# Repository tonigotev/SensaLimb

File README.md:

# SensaLimb

Smart arm prosthesis project.

## ML Model (Latest Recommended): Toro Ossaba Conv1D

Use this model family as the current default:

- Model family folder: `ML/models/conv1d_angle_toro_ossaba`
- Dataset folder (required): `ML/datasets/Toro Ossaba`
- Training script: `ML/train/train_conv1d_angle_toro_ossaba.py`

## 1) Install ML dependencies

From the repository root (PowerShell):

```powershell
python -m pip install --upgrade pip
python -m pip install -r requirements-ml.txt
```

## 2) Download and extract the Toro Ossaba dataset (required)

Dataset source:

- https://zenodo.org/records/7946782

Extract location must be exactly:

- `ML/datasets/Toro Ossaba`

Important extraction rule:

- After extraction, your `.txt` dataset files must be inside `ML/datasets/Toro Ossaba/...` (subject subfolders).
- Do **not** leave the files nested one level too deep (for example, avoid `ML/datasets/Toro Ossaba/Toro Ossaba/...`).

Quick check (PowerShell):

```powershell
Get-ChildItem "ML/datasets/Toro Ossaba" -Recurse -Filter *.txt | Select-Object -First 5 FullName
```

## 3) Install/extract the Toro Ossaba trained model files

If you received model files as a zip/archive, extract them into:

- `ML/models/conv1d_angle_toro_ossaba`

Expected model artifacts in the selected run folder:

- `model.keras`
- `model.tflite`
- `model_int8.tflite` (optional but recommended for embedded use)
- `meta.json`

Example expected path pattern:

- `ML/models/conv1d_angle_toro_ossaba/<run_name>/model.tflite`

If your extraction creates an extra folder level, move files so that the run folder directly contains `meta.json` and model files.

## 4) Run the model (inference/validation)

Pick your run folder (example):

```powershell
$MODEL_DIR = "ML/models/conv1d_angle_toro_ossaba/seed9_20260117_034451_884"
```

### A. Compare float vs int8 model outputs

```powershell
python ML/tools/compare_tflite_models.py --model-dir "$MODEL_DIR" --input-root "ML/datasets/Toro Ossaba" --samples 50
```

### B. Generate prediction-vs-true plots

```powershell
python ML/tools/plot_tflite_pred_vs_true.py --model-dir "$MODEL_DIR" --input-root "ML/datasets/Toro Ossaba" --samples 2000
```

Output images are saved in the same run folder:

- `pred_vs_true_float.png`
- `pred_vs_true_int8.png`

## 5) (Optional) Train a new Toro Ossaba model run

```powershell
python ML/train/train_conv1d_angle_toro_ossaba.py --use-file-split --movement all --emg-source filtered --angle-history-sec 0.1 --tflite-int8 --seed 9 --run-name seed9_new
```

This creates a new run folder under `ML/models/conv1d_angle_toro_ossaba`.

## Common setup mistakes

- Dataset extracted to wrong folder (must be `ML/datasets/Toro Ossaba`).
- Extra nested folder after extraction.
- Model archive extracted to wrong location.
- Missing `model.tflite` / `meta.json` in selected run folder.

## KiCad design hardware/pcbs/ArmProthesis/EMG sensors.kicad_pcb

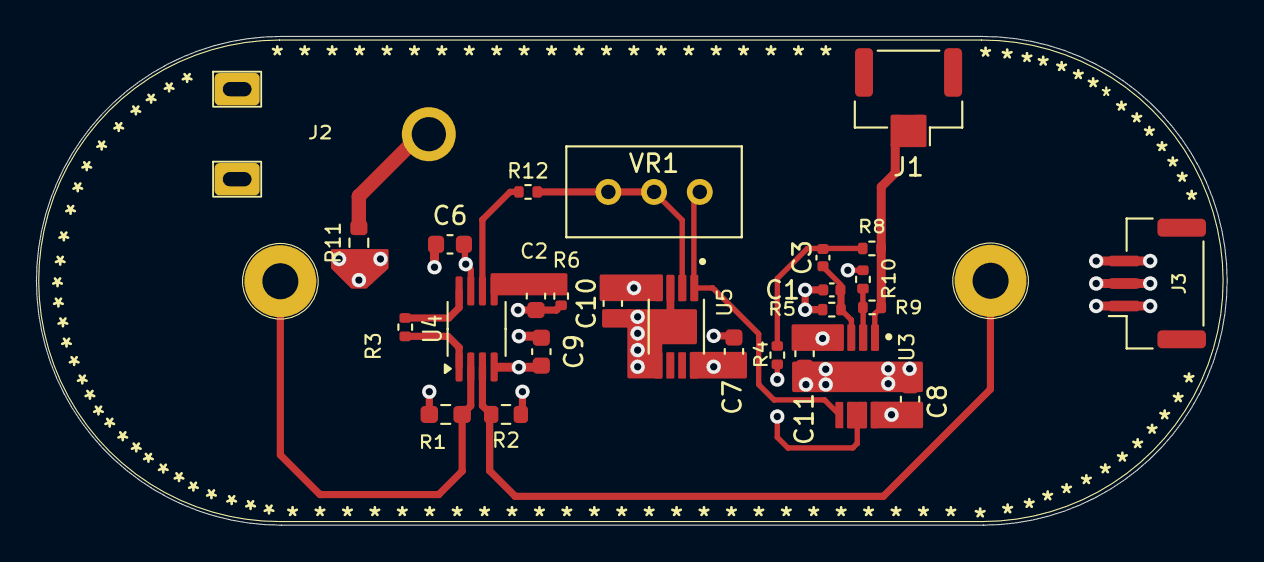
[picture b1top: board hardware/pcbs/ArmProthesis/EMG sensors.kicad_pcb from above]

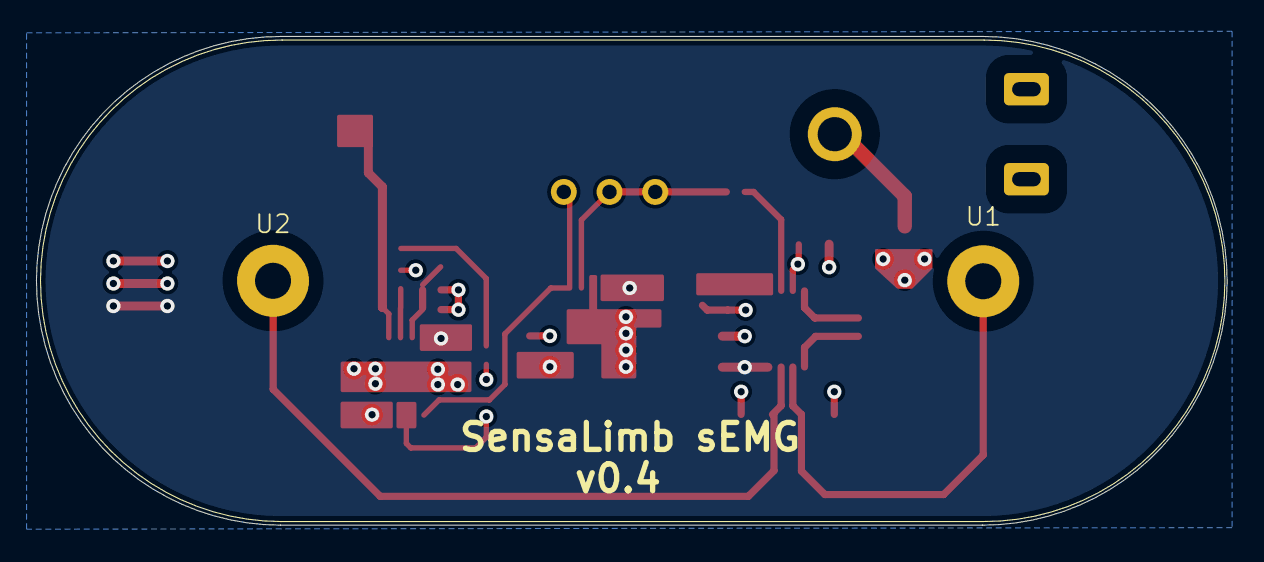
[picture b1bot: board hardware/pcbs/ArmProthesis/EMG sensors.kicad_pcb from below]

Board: 4 copper layers, 66.2 x 27.1 mm, 29 parts (2 on the bottom side), 17 nets.

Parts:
C1: 10uF; C_0402_1005Metric
C2: DNP; C_0603_1608Metric
C3: 330nF; C_0402_1005Metric
C6, C7, C8, C9, C10, C11: 1uF; C_0603_1608Metric
J1: Conn_01x02_Pin; JST_GH_SM02B-GHS-TB_1x02-1MP_P1.25mm_Horizontal
J2: DNP; DIN_Male_1PIN_1.5mm
J3: Conn_01x03_Pin; JST_GH_SM03B-GHS-TB_1x03-1MP_P1.25mm_Horizontal
R1: 10M; R_0603_1608Metric_Pad0.98x0.95mm_HandSolder
R2: 10M; R_0603_1608Metric
R3: 2k; R_0402_1005Metric
R4, R5, R8, R10: 1k; R_0402_1005Metric
R6: 249k; R_0402_1005Metric
R9, R12: 10k; R_0402_1005Metric
R11: 1M; R_0603_1608Metric
U1, U2: EMG_Snap_4mm
U3, U5: LME49726MY
U4: INA326; MSOP-8_3x3mm_P0.65mm
VR1: 100k; Potentiometer_Bourns_3296W_Vertical

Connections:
/+2.5V: C6.1, C7.1, C8.1, J3.3, R11.1, U3.8 (VDD), U4.7 (V+), U5.8 (VDD)
/-2.5V: C9.1, C10.1, C11.1, J3.1, U3.4 (VSS), U4.4 (V-), U5.4 (VSS)
/AEMG: J1.1, J1.2, R8.1, R9.2, U3.1 (OUT_A)
FB: R9.1, R10.2, U3.2 (NEGA)
GND: C1.1, C2.1, C6.2, C7.2, C8.2, C9.2, C10.2, C11.2, J3.2, R1.1, R2.1, R5.1, R6.1, R10.1, U3.9 (EP), U5.3 (POSA), U5.5 (POSB), U5.9 (EP)
INVERTED: U3.5 (POSB), U5.1 (OUT_A), VR1.3
unnamed: C3.2, R4.2, R8.2
unnamed: J2.1, R11.2
unnamed: R3.1, U4.8 (R1)
unnamed: R3.2, U4.1 (R1)
unnamed: R12.1, U4.6
unnamed: C1.2, C3.1, R5.2, U3.3 (POSA)
unnamed: C2.2, R6.2, U4.5 (R2)
unnamed: R12.2, U5.2 (NEGA), VR1.1, VR1.2
Vin1: R1.2, U1.1, U4.2 (-)
Vin2: R2.2, U2.1, U4.3 (+)
non-filtered: R4.1, U3.6 (NEGB), U3.7 (OUT_B)

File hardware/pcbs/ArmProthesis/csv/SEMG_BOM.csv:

"Reference","Value","Footprint","Qty","LCSC"
"VR1","100k","Potentiometer_THT:Potentiometer_Bourns_3296W_Vertical","1","C48084"
"U5","LME49726MY","OP AMPS:LME49726MY","1","C128880"
"U4","INA326","Package_SO:MSOP-8_3x3mm_P0.65mm","1","C179740"
"U3","LME49726MY","OP AMPS:LME49726MY","1","C128880"
"U2","DNP","EMG:EMG_Snap_4mm","1",""
"U1","DNP","EMG:EMG_Snap_4mm","1",""
"R12","10k","Resistor_SMD:R_0402_1005Metric","1","C25744"
"R11","1M","Resistor_SMD:R_0603_1608Metric","1","C22935"
"R10","1k","Resistor_SMD:R_0402_1005Metric","1","C106235"
"R9","10k","Resistor_SMD:R_0402_1005Metric","1","C25744"
"R8","1k","Resistor_SMD:R_0402_1005Metric","1","C106235"
"R6","249k","Resistor_SMD:R_0402_1005Metric","1","C226368"
"R5","1k","Resistor_SMD:R_0402_1005Metric","1","C106235"
"R4","1k","Resistor_SMD:R_0402_1005Metric","1","C106235"
"R3","2k","Resistor_SMD:R_0402_1005Metric","1","C60488"
"R2","10M","Resistor_SMD:R_0603_1608Metric","1","C7250"
"R1","10M","Resistor_SMD:R_0603_1608Metric","1","C7250"
"J4","DNP","Connectors:DIN_Male_1PIN_1.5mm","1",""
"J3","Conn_01x03_Pin","Connector_JST:JST_GH_SM03B-GHS-TB_1x03-1MP_P1.25mm_Horizontal","1","C514175"
"J2","DNP","Connectors:DIN_Male_1PIN_1.5mm","1",""
"C11","1uF","Capacitor_SMD:C_0603_1608Metric","1","C15849"
"C10","1uF","Capacitor_SMD:C_0603_1608Metric","1","C15849"
"C9","1uF","Capacitor_SMD:C_0603_1608Metric","1","C15849"
"C8","1uF","Capacitor_SMD:C_0603_1608Metric","1","C15849"
"C7","1uF","Capacitor_SMD:C_0603_1608Metric","1","C15849"
"C6","1uF","Capacitor_SMD:C_0603_1608Metric","1","C15849"
"C3","330nF","Capacitor_SMD:C_0402_1005Metric","1","C47118439"
"C2","DNP","Capacitor_SMD:C_0603_1608Metric","1",""
"C1","10uF","Capacitor_SMD:C_0402_1005Metric","1","C6119763"

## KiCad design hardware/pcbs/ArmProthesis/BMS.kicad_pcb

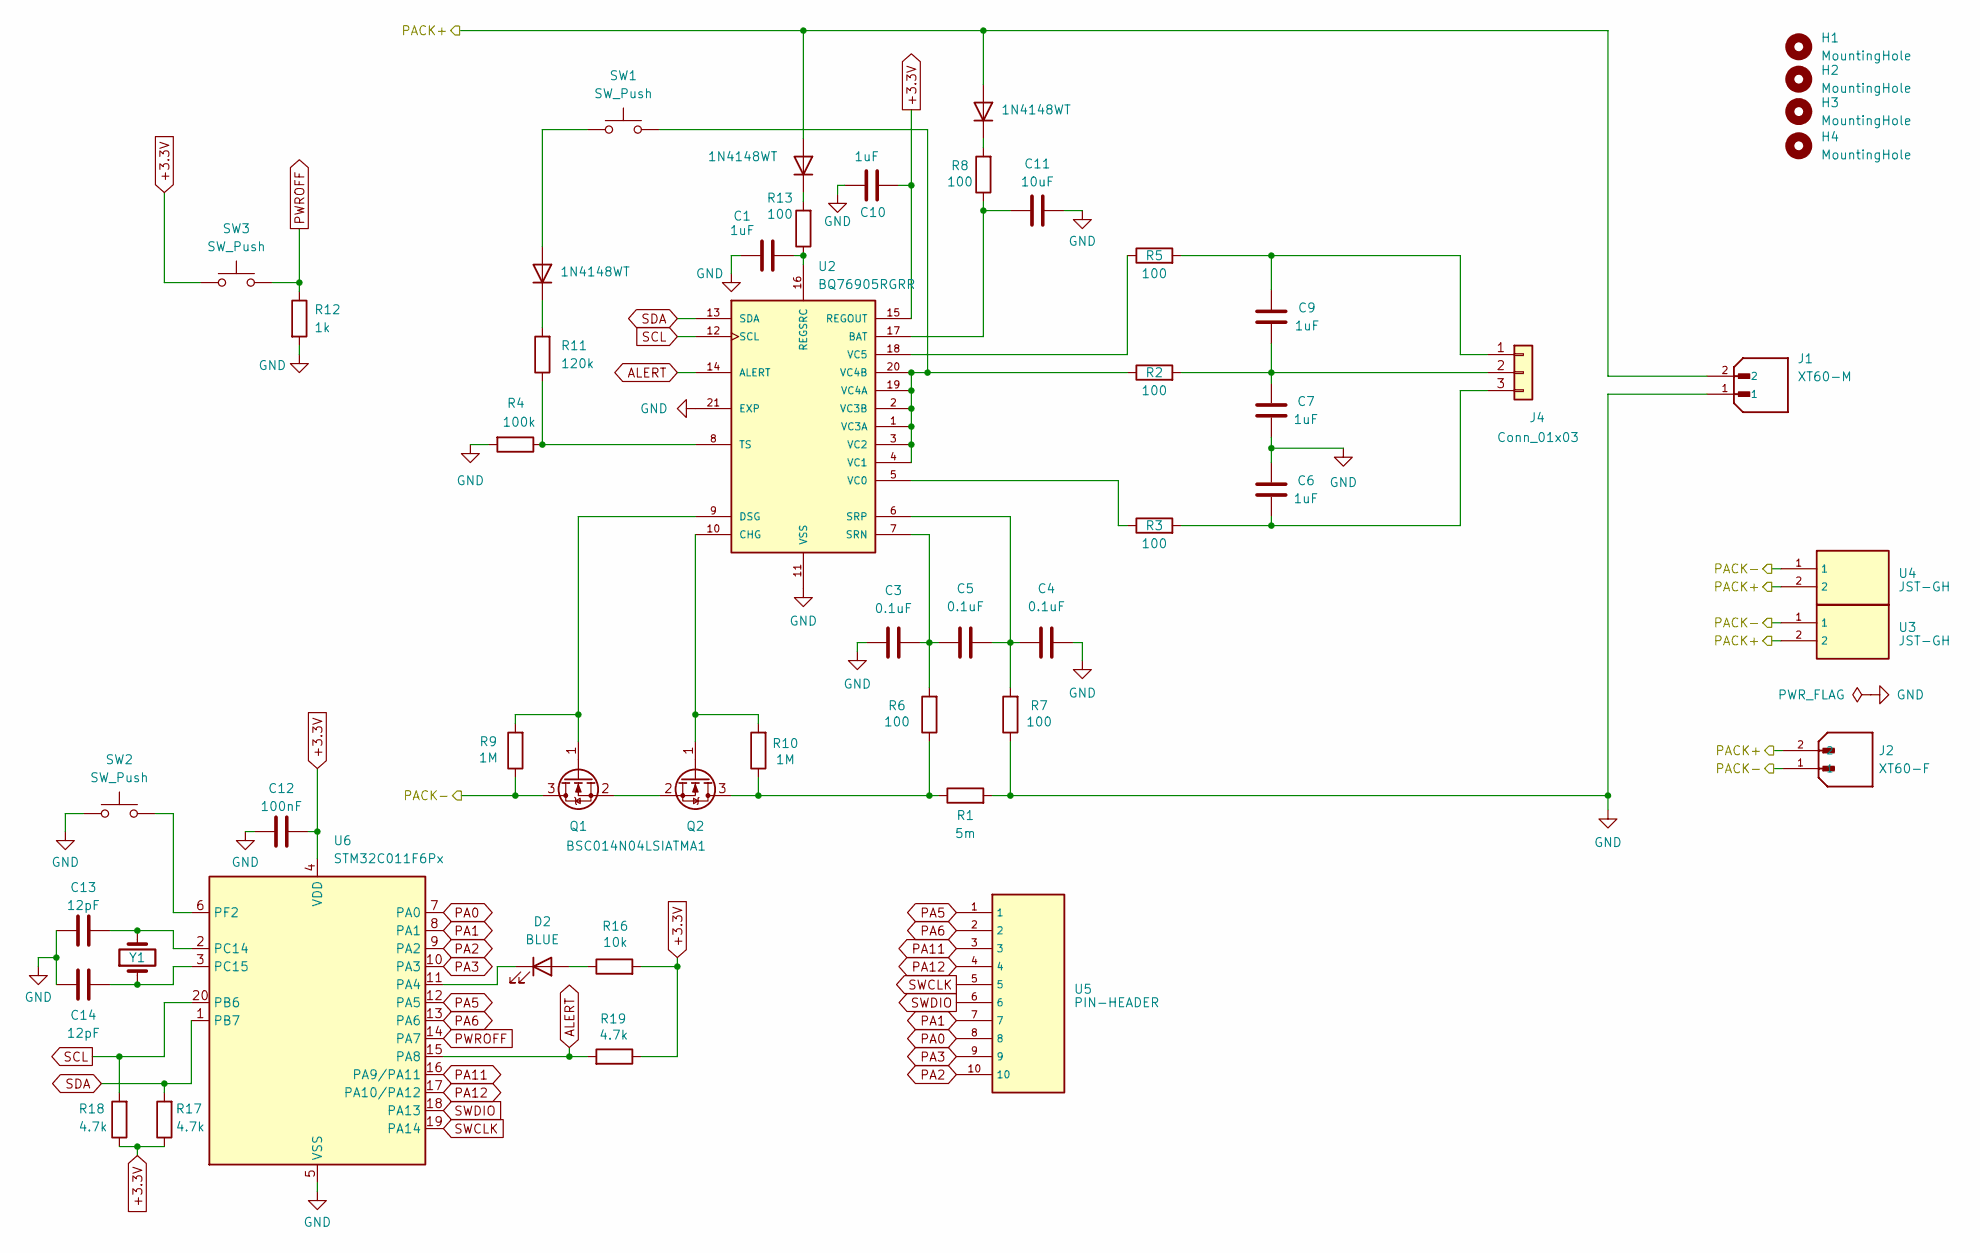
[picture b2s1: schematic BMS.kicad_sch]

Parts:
C1, C6, C7, C9: 1uF; C_0603_1608Metric; LCSC C15849
C3, C4, C5: 0.1uF; C_0603_1608Metric; LCSC C14663
C10: 1uF; C_0402_1005Metric; LCSC C14445
C11: 10uF; C_1206_3216Metric; LCSC C105197
C12: 100nF; C_0402_1005Metric; LCSC C110251
C13, C14: 12pF; C_0603_1608Metric; LCSC C346206
D1, D3, D4: 1N4148WT; D_SOD-523; LCSC C232841
D2: BLUE; D_0603_1608Metric; LCSC C282129
H1, H2, H3, H4: MountingHole; MountingHole_3.2mm_M3_DIN965
J1: XT60-M; AMASS_XT60PW-M_1x02_P7.20mm_Horizontal; PARTREV V1.2; LCSC C98732
J2: XT60-F; AMASS_XT60PW-F_1x02_P7.20mm_Horizontal; PARTREV V1.2; LCSC C428722
J4: Conn_01x03; JST_GH_SM03B-GHS-TB_1x03-1MP_P1.25mm_Horizontal; LCSC C514175
Q1, Q2: BSC014N04LSIATMA1; TRANS_BSC014N04LSIATMA1; LCSC C2934854
R1: 5m; R_2512_6332Metric; LCSC C22385263
R2, R3, R5, R6, R7, R8, R13: 100; R_0402_1005Metric; LCSC C106232
R4: 100k; R_0402_1005Metric; LCSC C25741
R9, R10: 1M; R_0603_1608Metric; LCSC C22935
R11: 120k; R_0402_1005Metric; LCSC C93945
R12: 1k; R_0402_1005Metric; LCSC C11702
R16: 10k; R_0402_1005Metric; LCSC C60490
R17, R18, R19: 4.7k; R_0402_1005Metric; LCSC C25900
SW1, SW2, SW3: SW_Push; SW_SPST_B3U-3000P; LCSC C963349
U2: BQ76905RGRR; PARTREV November 2023; LCSC C22394458
U3, U4: JST-GH; JST_GH_SM02B-GHS-TB_1x02-1MP_P1.25mm_Horizontal; LCSC C189893
U5: PIN-HEADER; PinHeader_2x05_P2.54mm_Horizontal; LCSC C492433
U6: STM32C011F6Px; TSSOP-20_4.4x6.5mm_P0.65mm; LCSC C5456198
Y1: YXC X321532768KGD2SI; NX3215SA-32.768K-STD-MUA-8; LCSC C620155

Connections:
+3.3V: C10.2, C12.1, R16.2, R17.1, R18.1, R19.1, SW3.1, U2.15 (REGOUT), U6.4 (VDD)
/PACK+: D3.2 (A), D4.2 (A), J1.2, J2.2, U3.2, U4.2
/PACK-: J2.1, Q1.3 (D), R9.1, U3.1, U4.1
ALERT: R19.2, U2.14 (ALERT), U6.15 (PA8)
GND: C1.1, C3.1, C4.1, C6.1, C7.2, C10.1, C11.1, C12.2, C13.2, C14.2, J1.1, R1.2, R4.2, R7.1, R12.2, SW2.1, U2.11 (VSS), U2.21 (EXP), U6.5 (VSS)
unnamed: D1.2 (A), SW1.1
unnamed: D1.1 (K), R11.2
unnamed: D2.2 (A), R16.1
unnamed: D2.1 (K), U6.11 (PA4)
unnamed: D3.1 (K), R8.2
unnamed: D4.1 (K), R13.2
unnamed: C9.1, J4.1, R5.2
unnamed: C7.1, C9.2, J4.2, R2.2
unnamed: C6.2, J4.3, R3.2
unnamed: Q1.1 (G), R9.2, U2.9 (DSG)
unnamed: Q1.2 (S), Q2.2 (S)
unnamed: Q2.3 (D), R1.1, R6.1, R10.1
unnamed: Q2.1 (G), R10.2, U2.10 (CHG)
unnamed: C11.2, R8.1, U2.17 (BAT)
unnamed: C1.2, R13.1, U2.16 (REGSRC)
unnamed: C3.2, C5.1, R6.2, U2.7 (SRN)
unnamed: C4.2, C5.2, R7.2, U2.6 (SRP)
unnamed: R4.1, R11.1, U2.8 (TS)
unnamed: R3.1, U2.5 (VC0)
unnamed: R2.1, SW1.2, U2.1 (VC3A), U2.2 (VC3B), U2.3 (VC2), U2.4 (VC1), U2.19 (VC4A), U2.20 (VC4B)
unnamed: R5.1, U2.18 (VC5)
unnamed: C13.1, U6.2 (PC14), Y1.2
unnamed: C14.1, U6.3 (PC15), Y1.1
unnamed: SW2.2, U6.6 (PF2)
PA0: U5.8, U6.7 (PA0)
PA1: U5.7, U6.8 (PA1)
PA2: U5.10, U6.9 (PA2)
PA3: U5.9, U6.10 (PA3)
PA5: U5.1, U6.12 (PA5)
PA6: U5.2, U6.13 (PA6)
PA11: U5.3, U6.16 (PA9/PA11)
PA12: U5.4, U6.17 (PA10/PA12)
PWROFF: R12.1, SW3.2, U6.14 (PA7)
SCL: R18.2, U2.12 (SCL), U6.20 (PB6)
SDA: R17.2, U2.13 (SDA), U6.1 (PB7)
SWCLK: U5.5, U6.19 (PA14)
SWDIO: U5.6, U6.18 (PA13)

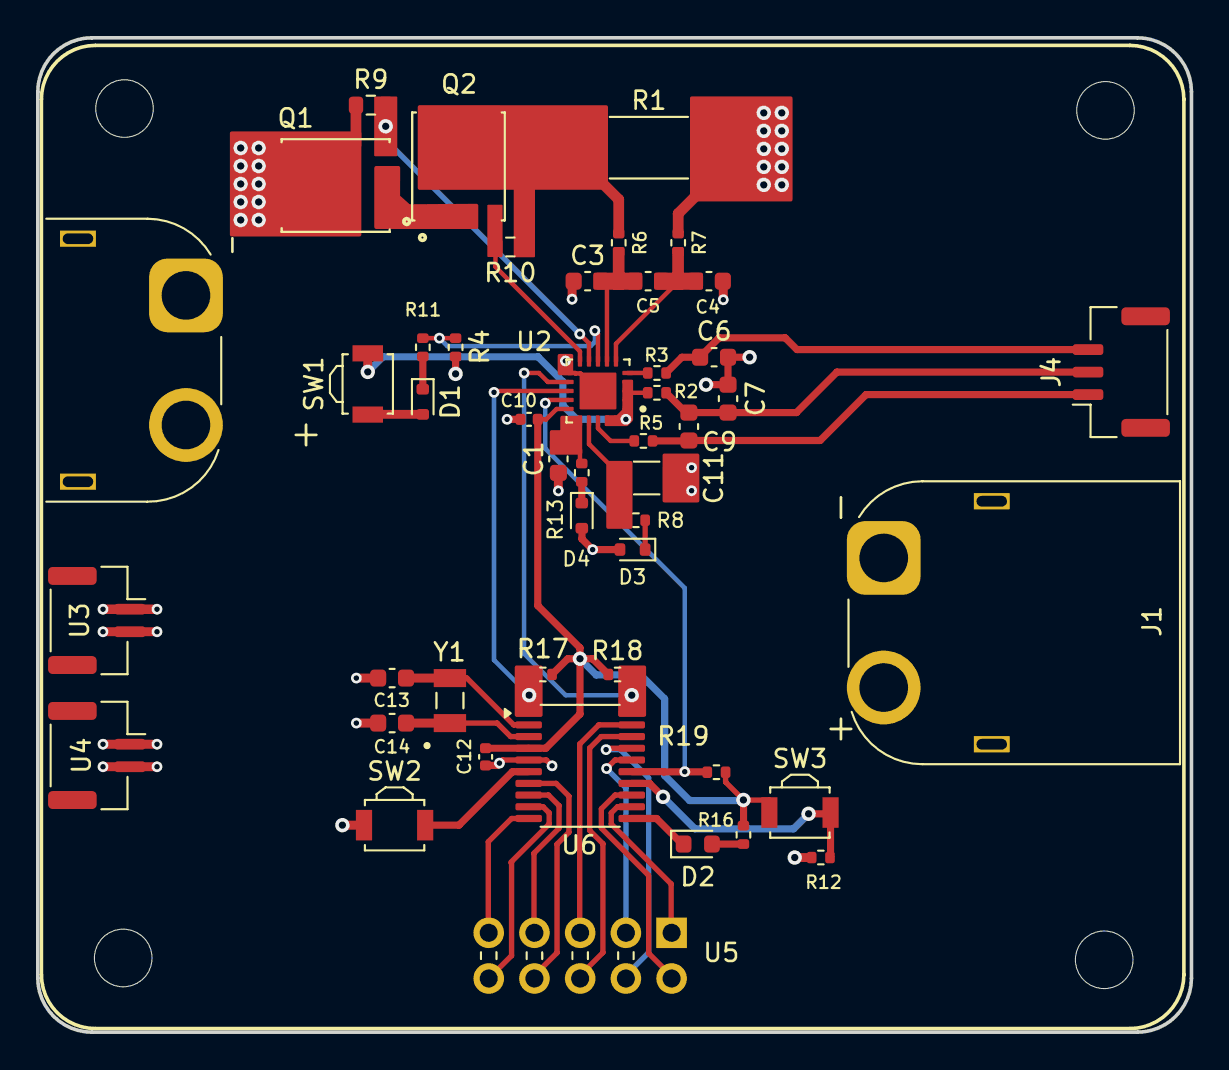
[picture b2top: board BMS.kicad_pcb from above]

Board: 4 copper layers, 64.1 x 55.2 mm, 51 parts (0 on the bottom side), 42 nets.

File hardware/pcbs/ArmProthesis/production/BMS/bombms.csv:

Designator,Footprint,Quantity,Value,LCSC Part #
"C1, C6, C7, C9",0603,4,1uF,C15849
C10,0402,1,1uF,C14445
C11,1206,1,10uF,C105197
C12,0402,1,100nF,C110251
"C13, C14",0603,2,12pF,C346206
"C3, C4, C5",0603,3,0.1uF,C14663
"D1, D3, D4",D_SOD-523,3,1N4148WT,C232841
D2,0603,1,BLUE,C282129
J1,AMASS_XT60PW-M_1x02_P7.20mm_Horizontal,1,XT60-M,C98732
J2,AMASS_XT60PW-F_1x02_P7.20mm_Horizontal,1,XT60-F,C428722
J4,JST_GH_SM03B-GHS-TB_1x03-1MP_P1.25mm_Horizontal,1,Conn_01x03,C514175
"Q1, Q2",TRANS_BSC014N04LSIATMA1,2,BSC014N04LSIATMA1,C2934854
R1,2512,1,5m,C22385263
"R10, R9",0603,2,1M,C22935
R11,0402,1,120k,C93945
R12,0402,1,1k,C11702
"R13, R2, R3, R5, R6, R7, R8",0402,7,100,C106232
R16,0402,1,10k,C60490
"R17, R18, R19",0402,3,4.7k,C25900
R4,0402,1,100k,C25741
"SW1, SW2, SW3",SW_SPST_B3U-3000P,3,SW_Push,C963349
U2,BQ76905RGRR,1,BQ76905RGRR,C22394458
"U3, U4",JST_GH_SM02B-GHS-TB_1x02-1MP_P1.25mm_Horizontal,2,JST-GH,C189893
U5,PinHeader_2x05_P2.54mm_Horizontal,1,PIN-HEADER,C492433
U6,TSSOP-20_4.4x6.5mm_P0.65mm,1,STM32C011F6Px,C5456198
Y1,NX3215SA-32.768K-STD-MUA-8,1,YXC X321532768KGD2SI,C620155

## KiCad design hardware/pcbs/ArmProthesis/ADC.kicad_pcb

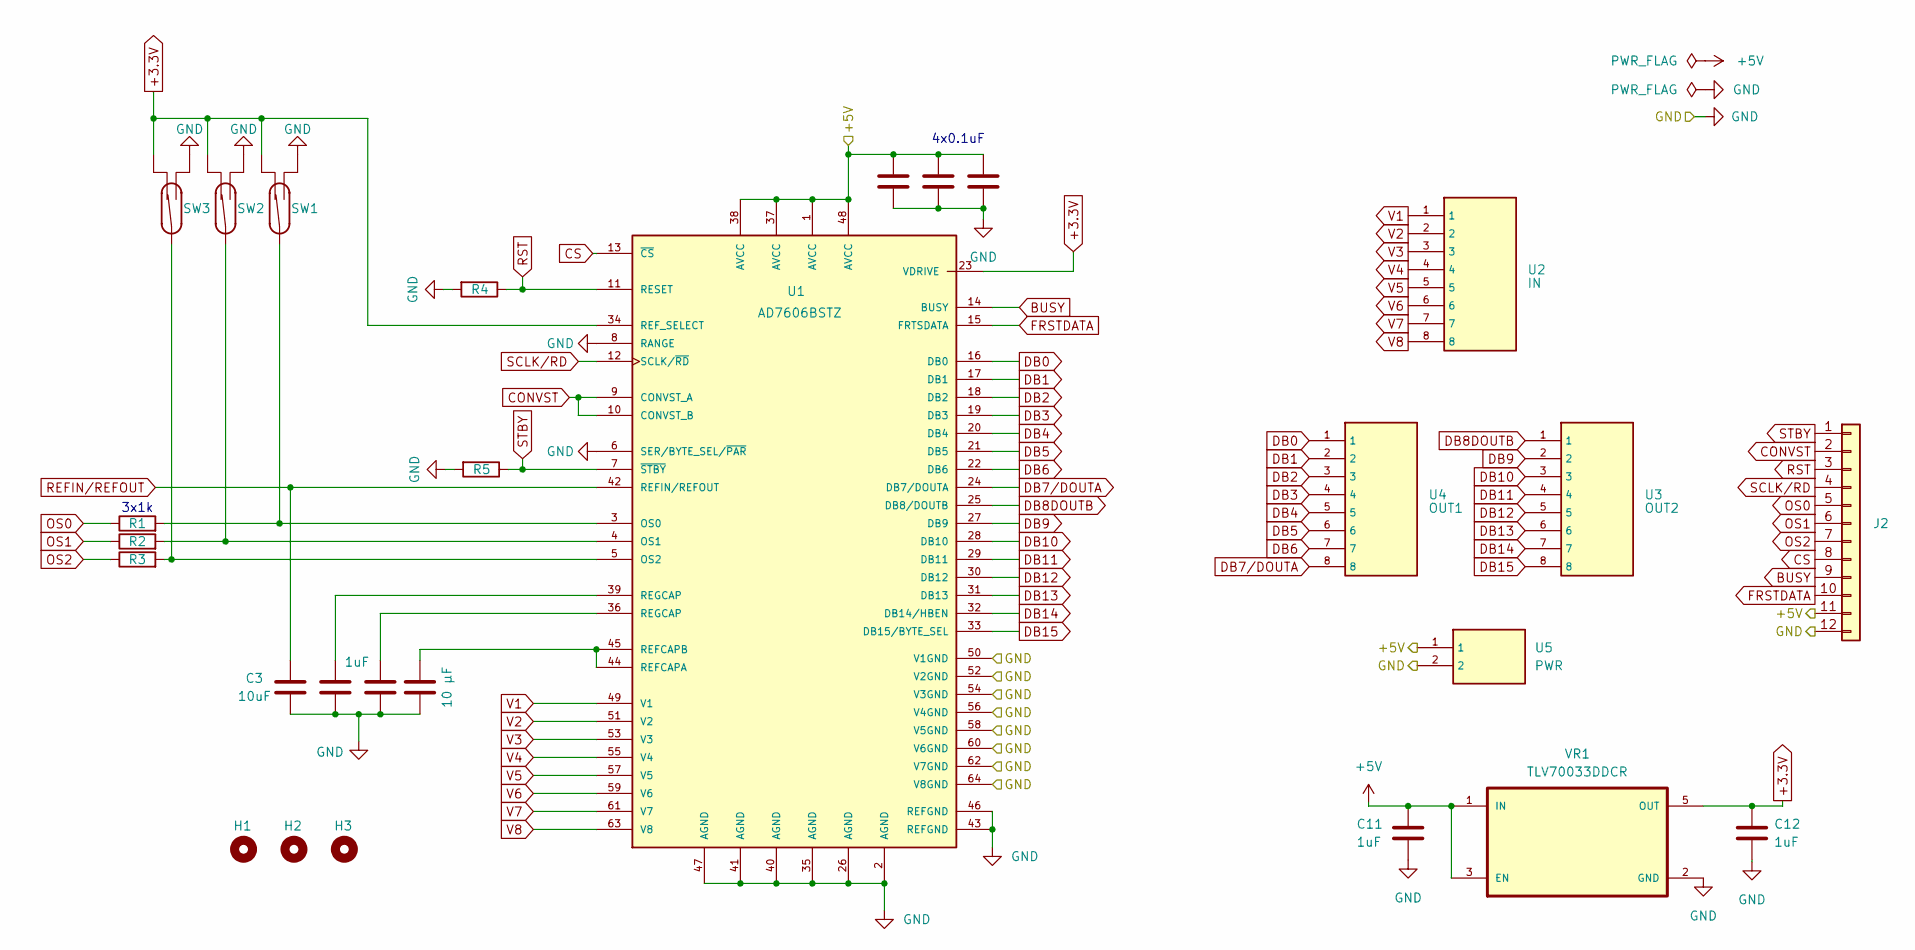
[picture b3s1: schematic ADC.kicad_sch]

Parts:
C2, C6, C11, C12: 1uF; C_0402_1005Metric; LCSC C52923
C3: 10uF; C_0603_1608Metric; LCSC C19702
C4, C8, C9: 0.1uF; C_0402_1005Metric; LCSC C307331
C7: 10 µF; C_0603_1608Metric; LCSC C19702
H1, H2, H3: MountingHole; MountingHole_2.7mm_M2.5
J2: SET; PinHeader_1x12_P2.54mm_Vertical; LCSC C725944
R1, R2, R3: 1k; R_0402_1005Metric; LCSC C11702
R4, R5: 10k; R_0603_1608Metric; LCSC C25804
SW1, SW2, SW3: SW_Reed_SPDT; SW_SPDT_Shouhan_MSK12C02; LCSC C431540
U1: AD7606BSTZ; LCSC C398827
U2: IN; JST_GH_SM08B-GHS-TB_1x08-1MP_P1.25mm_Horizontal; LCSC C265111
U3: OUT2; JST_SH_SM08B-SRSS-TB_1x08-1MP_P1.00mm_Horizontal; LCSC C160407
U4: OUT1; JST_SH_SM08B-SRSS-TB_1x08-1MP_P1.00mm_Horizontal; LCSC C160407
U5: PWR; JST_GH_SM02B-GHS-TB_1x02-1MP_P1.25mm_Horizontal; LCSC C189893
VR1: TLV70033DDCR; LCSC C11337

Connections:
+3.3V: C12.1, SW1.1, SW2.1, SW3.1, U1.23 (VDRIVE), U1.34 (REF_SELECT), VR1.5 (OUT); also elsewhere on the board
+5V: C4.2, C8.2, C9.2, C11.1, J2.11, U1.1 (AVCC), U1.37 (AVCC), U1.38 (AVCC), U1.48 (AVCC), U5.1, VR1.1 (IN), VR1.3 (EN)
BUSY: J2.9, U1.14 (BUSY)
CONVST: J2.2, U1.9 (CONVST_A), U1.10 (CONVST_B)
CS: J2.8, U1.13 (~CS)
DB0: U1.16 (DB0), U4.1
DB1: U1.17 (DB1), U4.2
DB2: U1.18 (DB2), U4.3
DB3: U1.19 (DB3), U4.4
DB4: U1.20 (DB4), U4.5
DB5: U1.21 (DB5), U4.6
DB6: U1.22 (DB6), U4.7
DB7/DOUTA: U1.24 (DB7/DOUTA), U4.8
DB8DOUTB: U1.25 (DB8/DOUTB), U3.1
DB9: U1.27 (DB9), U3.2
DB10: U1.28 (DB10), U3.3
DB11: U1.29 (DB11), U3.4
DB12: U1.30 (DB12), U3.5
DB13: U1.31 (DB13), U3.6
DB14: U1.32 (DB14/HBEN), U3.7
DB15: U1.33 (DB15/BYTE_SEL), U3.8
FRSTDATA: J2.10, U1.15 (FRTSDATA)
GND: C2.1, C3.1, C4.1, C6.1, C7.2, C8.1, C9.1, C11.2, C12.2, J2.12, R4.2, R5.2, SW1.3, SW2.3, SW3.3, U1.2 (AGND), U1.6 (SER/BYTE_SEL/~PAR), U1.8 (RANGE), U1.26 (AGND), U1.35 (AGND), U1.40 (AGND), U1.41 (AGND), U1.43 (REFGND), U1.46 (REFGND), U1.47 (AGND), U1.50 (V1GND), U1.52 (V2GND), U1.54 (V3GND), U1.56 (V4GND), U1.58 (V5GND), U1.60 (V6GND), U1.62 (V7GND), U1.64 (V8GND), U5.2, VR1.2 (GND); also elsewhere on the board
unnamed: C2.2, U1.36 (REGCAP)
unnamed: C6.2, U1.39 (REGCAP)
unnamed: R1.2, SW1.2, U1.3 (OS0)
unnamed: R2.2, SW2.2, U1.4 (OS1)
unnamed: R3.2, SW3.2, U1.5 (OS2)
unnamed: C7.1, U1.44 (REFCAPA), U1.45 (REFCAPB)
OS0: J2.5, R1.1
OS1: J2.6, R2.1
OS2: J2.7, R3.1
REFIN/REFOUT: C3.2, U1.42 (REFIN/REFOUT)
RST: J2.3, R4.1, U1.11 (RESET)
SCLK/RD: J2.4, U1.12 (SCLK/~RD)
STBY: J2.1, R5.1, U1.7 (~STBY)
V1: U1.49 (V1), U2.1
V2: U1.51 (V2), U2.2
V3: U1.53 (V3), U2.3
V4: U1.55 (V4), U2.4
V5: U1.57 (V5), U2.5
V6: U1.59 (V6), U2.6
V7: U1.61 (V7), U2.7
V8: U1.63 (V8), U2.8

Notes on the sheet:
3x1k
4x0.1uF

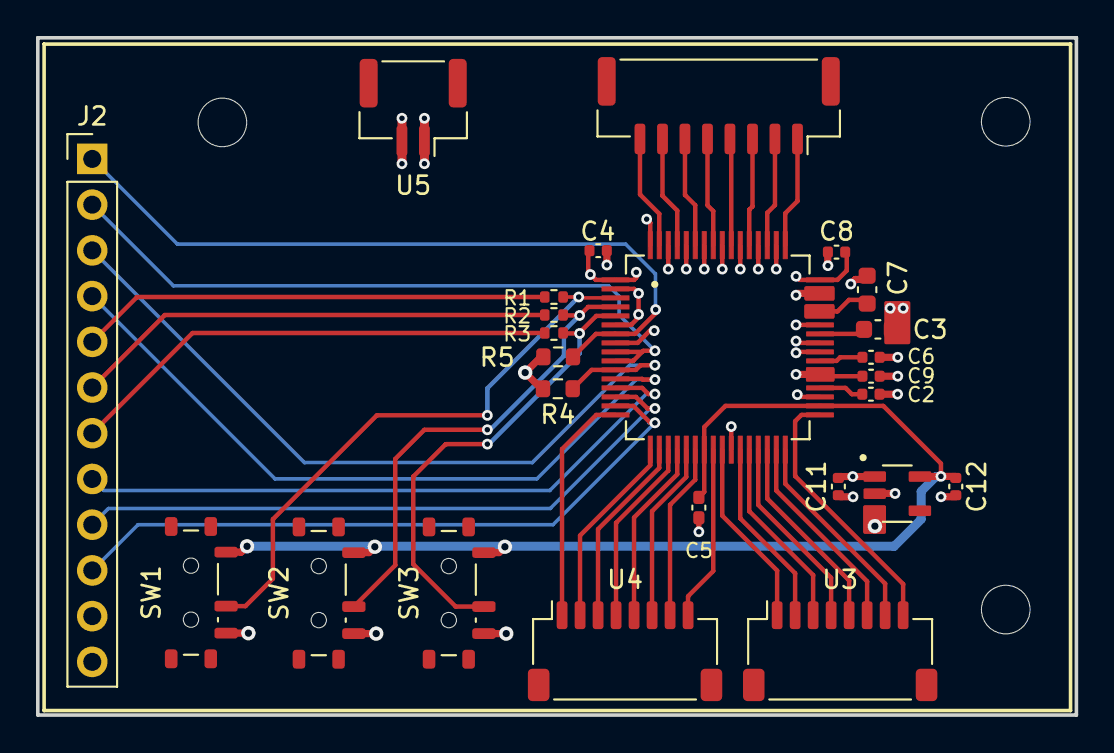
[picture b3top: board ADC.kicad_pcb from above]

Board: 4 copper layers, 57.7 x 37.6 mm, 28 parts (0 on the bottom side), 44 nets.

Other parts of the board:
C5: 0.1uF; C_0402_1005Metric_Pad0.74x0.62mm_HandSolder

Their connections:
+3.3V: C5.2; also elsewhere on the board
GND: C5.1; also elsewhere on the board

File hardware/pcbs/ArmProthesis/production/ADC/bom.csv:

Designator,Footprint,Quantity,Value,LCSC Part #
"C11, C12, C2, C6",0402,4,1uF,C52923
C3,0603,1,10uF,C19702
"C4, C8, C9",0402,3,0.1uF,C307331
C5,0402,1,0.1uF,
C7,0603,1,10 µF,C19702
J2,PinHeader_1x12_P2.54mm_Vertical,1,~,C725944
"R1, R2, R3",0402,3,1k,C11702
"R4, R5",0603,2,10k,C25804
"SW1, SW2, SW3",SW_SPDT_Shouhan_MSK12C02,3,SW_Reed_SPDT,C431540
U1,AD7606BSTZ,1,AD7606BSTZ,C398827
U2,JST_GH_SM08B-GHS-TB_1x08-1MP_P1.25mm_Horizontal,1,~,C265111
"U3, U4",JST_SH_SM08B-SRSS-TB_1x08-1MP_P1.00mm_Horizontal,2,~,C160407
U5,JST_GH_SM02B-GHS-TB_1x02-1MP_P1.25mm_Horizontal,1,~,C189893
VR1,TLV70033DDCR,1,TLV70033DDCR,C11337

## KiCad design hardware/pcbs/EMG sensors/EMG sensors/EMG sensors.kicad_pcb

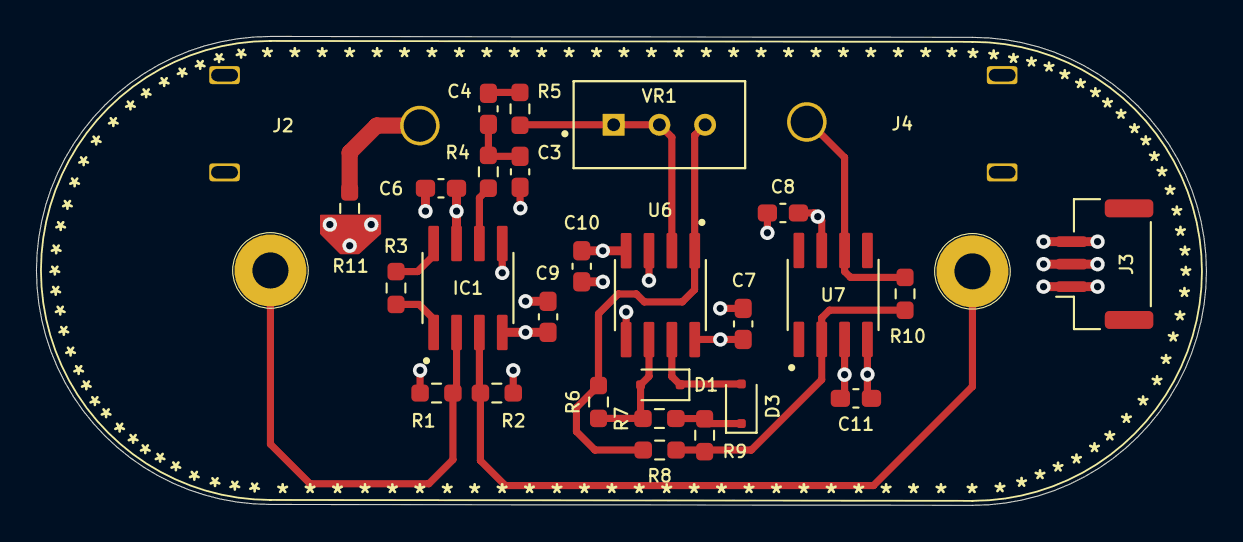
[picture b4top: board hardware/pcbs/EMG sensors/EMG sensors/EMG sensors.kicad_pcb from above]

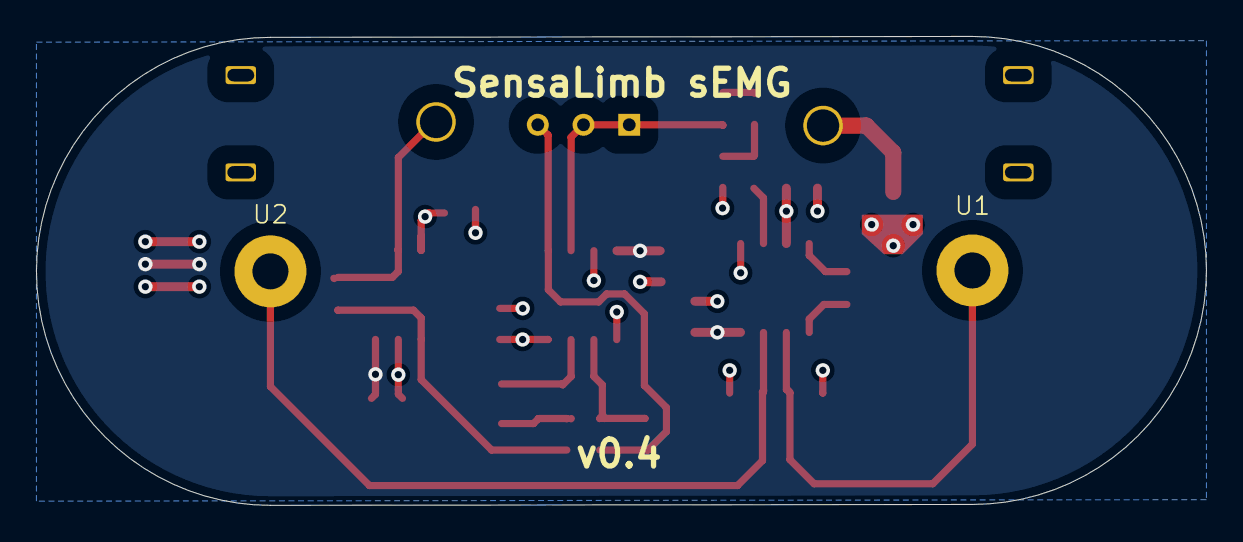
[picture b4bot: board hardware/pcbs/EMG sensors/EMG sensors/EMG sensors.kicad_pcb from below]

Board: 4 copper layers, 65.0 x 26.0 mm, 30 parts (2 on the bottom side), 18 nets.

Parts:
C3: 8.2nF; C_0603_1608Metric_Pad1.08x0.95mm_HandSolder
C4, C6, C7, C8, C9, C10, C11: 1uF; C_0603_1608Metric_Pad1.08x0.95mm_HandSolder
D1, D3: BAT54J; D_SOD-323F
IC1: INA128; INA128U
J2, J4: Conn_01x01_Pin; DIN_Male_1PIN_1.5mm
J3: Conn_01x03_Pin; JST_GH_SM03B-GHS-TB_1x03-1MP_P1.25mm_Horizontal
R1, R2: 10M; R_0603_1608Metric_Pad0.98x0.95mm_HandSolder
R3: 200; R_0603_1608Metric_Pad0.98x0.95mm_HandSolder
R4, R5, R9: 10k; R_0603_1608Metric_Pad0.98x0.95mm_HandSolder
R6, R7, R8, R10: 20k; R_0603_1608Metric_Pad0.98x0.95mm_HandSolder
R11: 1M; R_0603_1608Metric_Pad0.98x0.95mm_HandSolder
U1, U2: EMG_Snap_4mm
U6: OPA2188AIDR; ОПА2188AIDR
U7: OPA188AIDR; OPA188
VR1: 100k; TRIM_3296W-1-104ALF

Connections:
/+5.5V: C6.1, C7.1, C8.1, IC1.7 (V+), J3.1, U6.8 (V+), U7.7 (V+)
/-5.5V: C9.1, C10.1, C11.1, IC1.4 (V-), J3.2, U6.4 (V-), U7.4 (V-)
/AEMG: J4.1, R10.2, U7.6 (OUT)
GND: C3.2, C6.2, C7.2, C8.2, C9.2, C10.2, C11.2, IC1.5, J3.3, R1.1, R2.2, R11.1, U6.3 (+INA), U6.5 (+INB), U7.3 (+IN)
INVERTED: R6.1, R8.2, U6.1 (OUTA), VR1.3
unnamed: C3.1, C4.2, R4.2
unnamed: C4.1, R5.2
unnamed: D1.2 (A), R6.2, R7.2, U6.6 (-INB)
unnamed: D1.1 (K), D3.2 (A), U6.7 (OUTB)
unnamed: D3.1 (K), R7.1, R9.1
unnamed: IC1.1, R3.2
unnamed: IC1.6, R4.1
unnamed: IC1.8, R3.1
unnamed: J2.1, R11.2
unnamed: R5.1, U6.2 (-INA), VR1.1, VR1.2
unnamed: R8.1, R9.2, R10.1, U7.2 (-IN)
Vin1: IC1.2, R1.2, U1.1
Vin2: IC1.3, R2.1, U2.1

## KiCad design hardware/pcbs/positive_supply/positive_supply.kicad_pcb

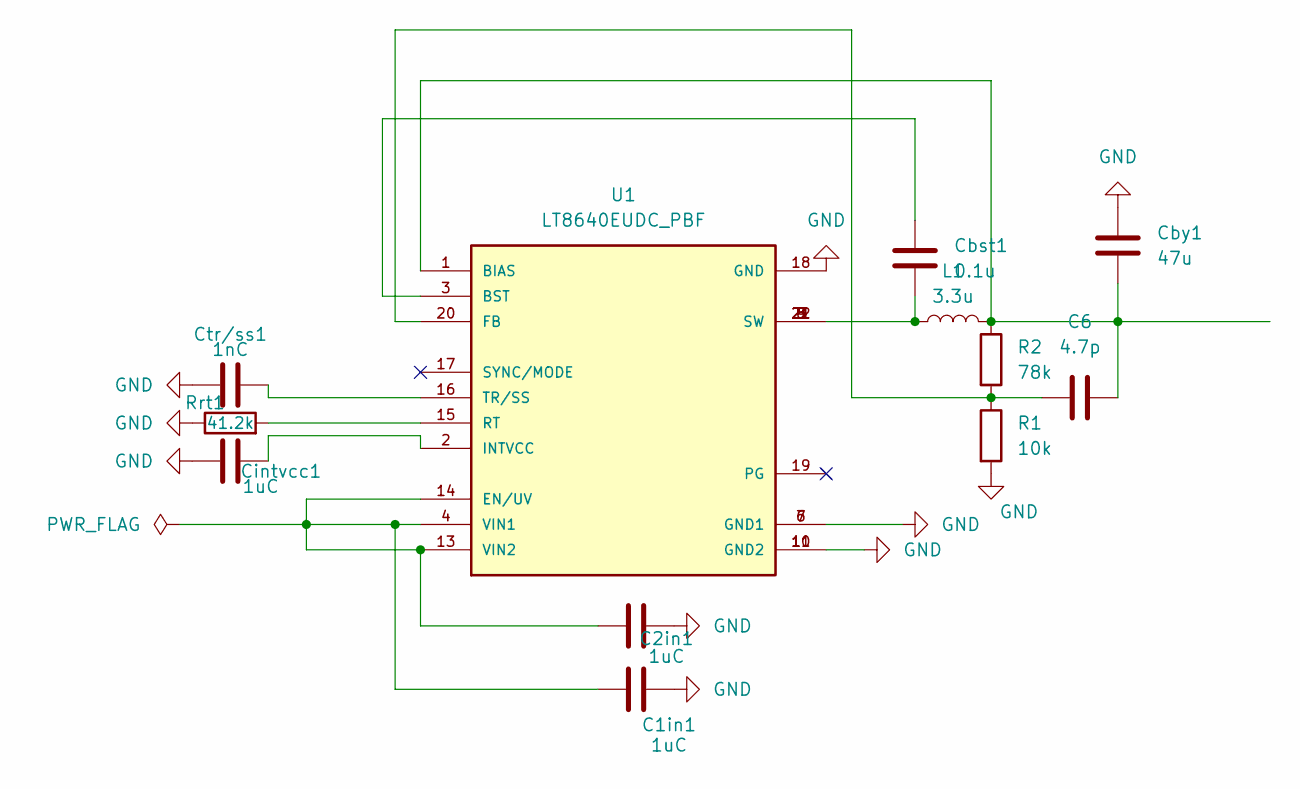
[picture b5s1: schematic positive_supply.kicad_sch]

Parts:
C1in1, C2in1: 1uC; C_0603_1608Metric_Pad1.08x0.95mm_HandSolder
C6: 4.7p; C_0603_1608Metric_Pad1.08x0.95mm_HandSolder
Cbst1: 0.1u; C_0603_1608Metric_Pad1.08x0.95mm_HandSolder
Cby1: 47u; C_3025_7563
Cintvcc1: 1uC; C_0603_1608Metric_Pad1.08x0.95mm_HandSolder
Ctr/ss1: 1nC; C_0603_1608Metric_Pad1.08x0.95mm_HandSolder
L1: 3.3u; IND_XAL5030-332MEC
R1: 10k; R_0402_1005Metric_Pad0.72x0.64mm_HandSolder
R2: 78k; R_0402_1005Metric_Pad0.72x0.64mm_HandSolder
Rrt1: 41.2k; R_0402_1005Metric_Pad0.72x0.64mm_HandSolder
U1: LT8640EUDC_PBF; QFN50P400X300X80-20N

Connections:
GND: C1in1.2, C2in1.2, Cby1.2, Cintvcc1.1, Ctr/ss1.1, R1.2, Rrt1.1, U1.6 (GND1), U1.7 (GND1), U1.10 (GND2), U1.11 (GND2), U1.18 (GND)
unnamed: Cbst1.2, L1.1, U1.8 (SW), U1.9 (SW), U1.21 (SW), U1.22 (SW)
unnamed: C6.2, Cby1.1, L1.2, R2.1, U1.1 (BIAS)
unnamed: Cbst1.1, U1.3 (BST)
unnamed: C1in1.1, C2in1.1, U1.4 (VIN1), U1.13 (VIN2), U1.14 (EN/UV)
unnamed: C6.1, R1.1, R2.2, U1.20 (FB)
unnamed: Cintvcc1.2, U1.2 (INTVCC)
unnamed: Rrt1.2, U1.15 (RT)
unnamed: Ctr/ss1.2, U1.16 (TR/SS)

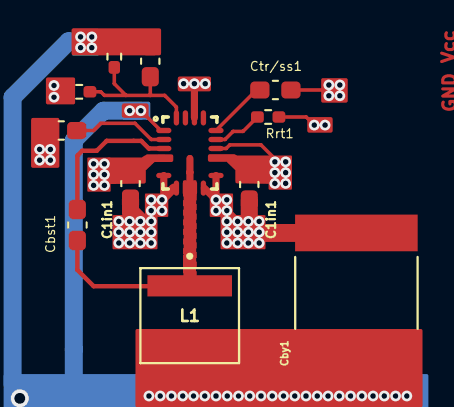
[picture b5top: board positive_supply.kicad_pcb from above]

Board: 4 copper layers, 12 parts (0 on the bottom side), 9 nets.

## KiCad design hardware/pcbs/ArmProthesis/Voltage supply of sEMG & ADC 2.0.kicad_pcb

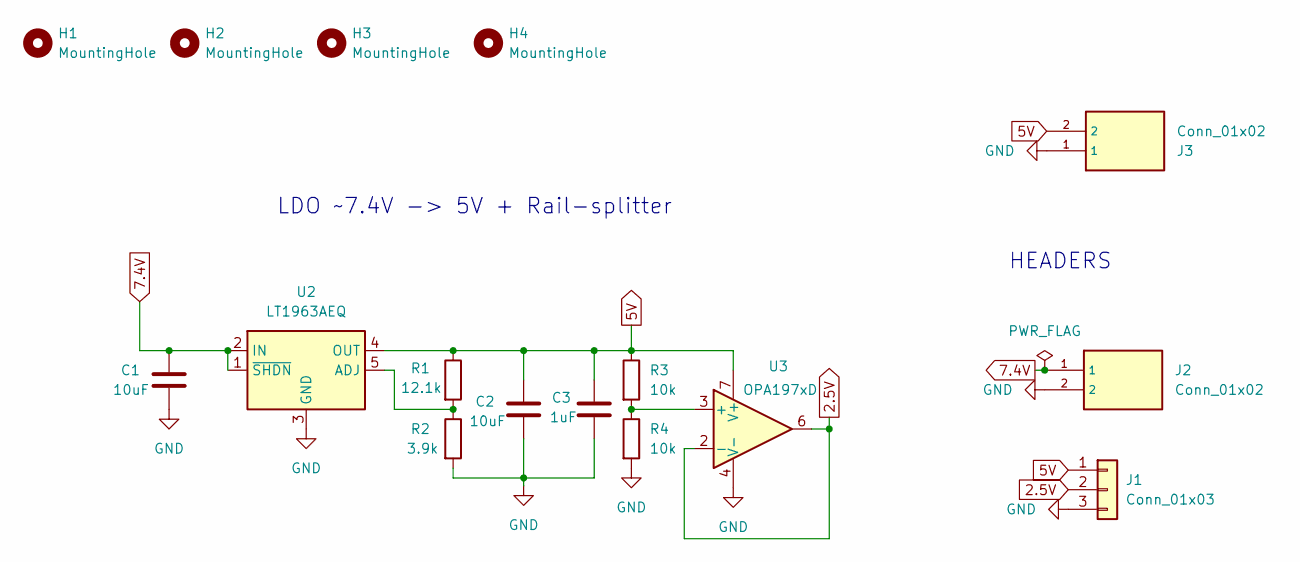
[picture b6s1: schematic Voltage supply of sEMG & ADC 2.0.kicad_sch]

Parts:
C1, C2: 10uF; C_0805_2012Metric; LCSC C92341
C3: 1uF; C_0603_1608Metric; LCSC C15849
H1, H2, H3, H4: MountingHole; MountingHole_2.7mm_M2.5_DIN965
J1: Conn_01x03; JST_GH_SM03B-GHS-TB_1x03-1MP_P1.25mm_Horizontal; LCSC C514175
J2, J3: Conn_01x02; JST_GH_SM02B-GHS-TB_1x02-1MP_P1.25mm_Horizontal; LCSC C189893
R1: 12.1k; R_0603_1608Metric; LCSC C22864
R2: 3.9k; R_0603_1608Metric; LCSC C114616
R3, R4: 10k; R_0402_1005Metric; LCSC C25744
U2: LT1963AEQ; TO-263-5_TabPin3; LCSC C107286
U3: OPA197xD; SOIC-8_3.9x4.9mm_P1.27mm; LCSC C1347124

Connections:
2.5V: J1.2, U3.2 (-), U3.6
5V: C2.1, C3.1, J1.1, J3.2, R1.1, R3.1, U2.4 (OUT), U3.7 (V+)
7.4V: C1.1, J2.1, U2.1 (~SHDN), U2.2 (IN)
GND: C1.2, C2.2, C3.2, J1.3, J2.2, J3.1, R2.2, R4.2, U2.3 (GND), U3.4 (V-)
unnamed: R1.2, R2.1, U2.5 (ADJ)
unnamed: R3.2, R4.1, U3.3 (+)

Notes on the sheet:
LDO ~7.4V -> 5V + Rail-splitter
HEADERS

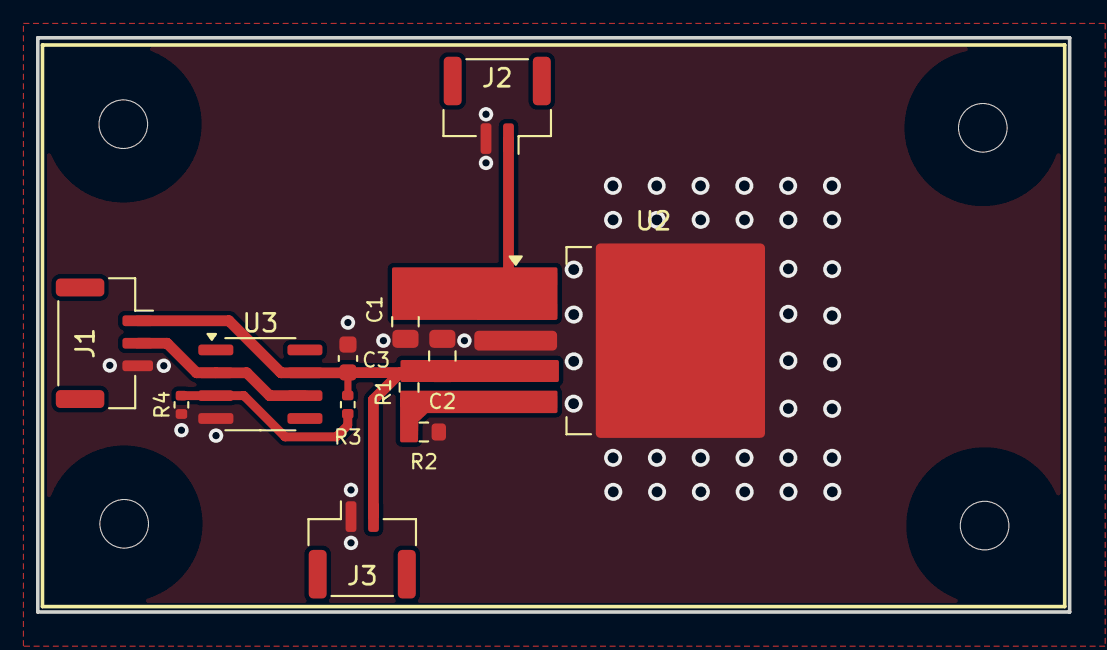
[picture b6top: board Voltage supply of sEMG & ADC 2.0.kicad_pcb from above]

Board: 2 copper layers, 57.3 x 31.9 mm, 16 parts (0 on the bottom side), 6 nets.

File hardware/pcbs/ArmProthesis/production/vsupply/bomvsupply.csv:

Designator,Footprint,Quantity,Value,LCSC Part #
"C1, C2",0805,2,10uF,C16194907
C3,0603,1,1uF,C15849
J1,JST_GH_SM03B-GHS-TB_1x03-1MP_P1.25mm_Horizontal,1,Conn_01x03,C514175
J2,JST_GH_SM02B-GHS-TB_1x02-1MP_P1.25mm_Horizontal,1,~,C189893
R1,0603,1,7.15k,C25980
R2,0603,1,1k,C21190
"R3, R4",0402,2,10k,C25744
U2,TO-263-5_TabPin3,1,LT1963AEQ,C107286
U3,SOIC-8_3.9x4.9mm_P1.27mm,1,OPA197xD,C1347124
